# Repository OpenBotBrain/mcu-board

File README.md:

# mcu-board

Some design notes for an MCU board...
Deeply WIP.

## Features

1. STM32 Cortex M4 with FSMC (possibility: STM32F413ZGT6 for 144-LQFP,
   STM32F413VGT3 for 100-LQFP, and STM32F413RGT6 for 64-LQFP)
2. Extra flash and PSRAM
2. WIFI module e.g. [ESP32 C3](https://www.espressif.com/sites/default/files/documentation/esp32-c3-mini-1_datasheet_en.pdf) or [ESP32 S3](https://www.espressif.com/sites/default/files/documentation/esp32-s3-mini-1_mini-1u_datasheet_en.pdf)
3. 4 motor control ports (EV3 compatible)
4. 4 sensor control ports (EV3 compatible)
5. Raspberry Pi pin-out connector (enough to communicate with
   Raspberry pi Zero, does not need full support)
5. SD card (SPI interface enough/SDIO nice to have but requires supported MCU)
6. Accelerometer (could be external)
7. STEMMA QT connector (nice to have)
8. Some informative display (nice to have)
9. A couple of buttons for interface (nice to have also)
10. Lego "compatible" physical shape.

### Alternative

- STM32L4R5VGT6 with 640KB of RAM instead of the external ram versions
  (but it also supports the FMC/FSMC). And it is cheap, and more
  available than the previous ones. (Or the subtly better STM32L4R5VIT6)

### Notes

- The [WIFI
  module](https://www.digikey.co.uk/en/products/detail/espressif-systems/ESP32-C3-MINI-1-H4/14548892)
  with the SD card on one side and the Raspberry Pi connector may not
  need to be active at the same time.
- The display could be controlled by the WIFI module via [AT
  commands](https://docs.espressif.com/projects/esp-at/en/latest/esp32/Compile_and_Develop/How_to_add_user-defined_AT_commands.html).
  Other things could be moved to the WIFI module too (the interface
  buttons, maybe).
- The board would be a [Raspberry Pi
  hat](https://github.com/raspberrypi/hats) that can work alone. This
  can be a rev 2 objective, but planning for the space would not hurt.
- Driving external memories with the FSMC, application not AN4761

# smaller mcu-board

## Features

1. STM32 Cortex M4 - May be
   - STM32L4P5CGT6
   - STM32L4P5CGT6P
   - STM32L4Q5CGT6
   - STM32L4Q5CGT6P
all (48-LQFP with 1MB of flash, and 320KB of RAM).

2. WIFI module e.g. [ESP32 C3](https://www.espressif.com/sites/default/files/documentation/esp32-c3-mini-1_datasheet_en.pdf) or [ESP32 S3](https://www.espressif.com/sites/default/files/documentation/esp32-s3-mini-1_mini-1u_datasheet_en.pdf)

3. 4 motor control ports (EV3 compatible)
4. 4 sensor control ports (EV3 compatible)

5. Raspberry Pi pin-out connector (enough to communicate with
   Raspberry pi Zero, does not need full support)

5. SD card (SPI interface enough/SDIO nice to have but requires supported MCU)
6. Accelerometer (could be external)
7. STEMMA QT connector (nice to have)
8. Some informative display and a couple of LEDs (nice to have)
9. A couple of buttons for interface (nice to have also)
10. Lego "compatible" physical shape.

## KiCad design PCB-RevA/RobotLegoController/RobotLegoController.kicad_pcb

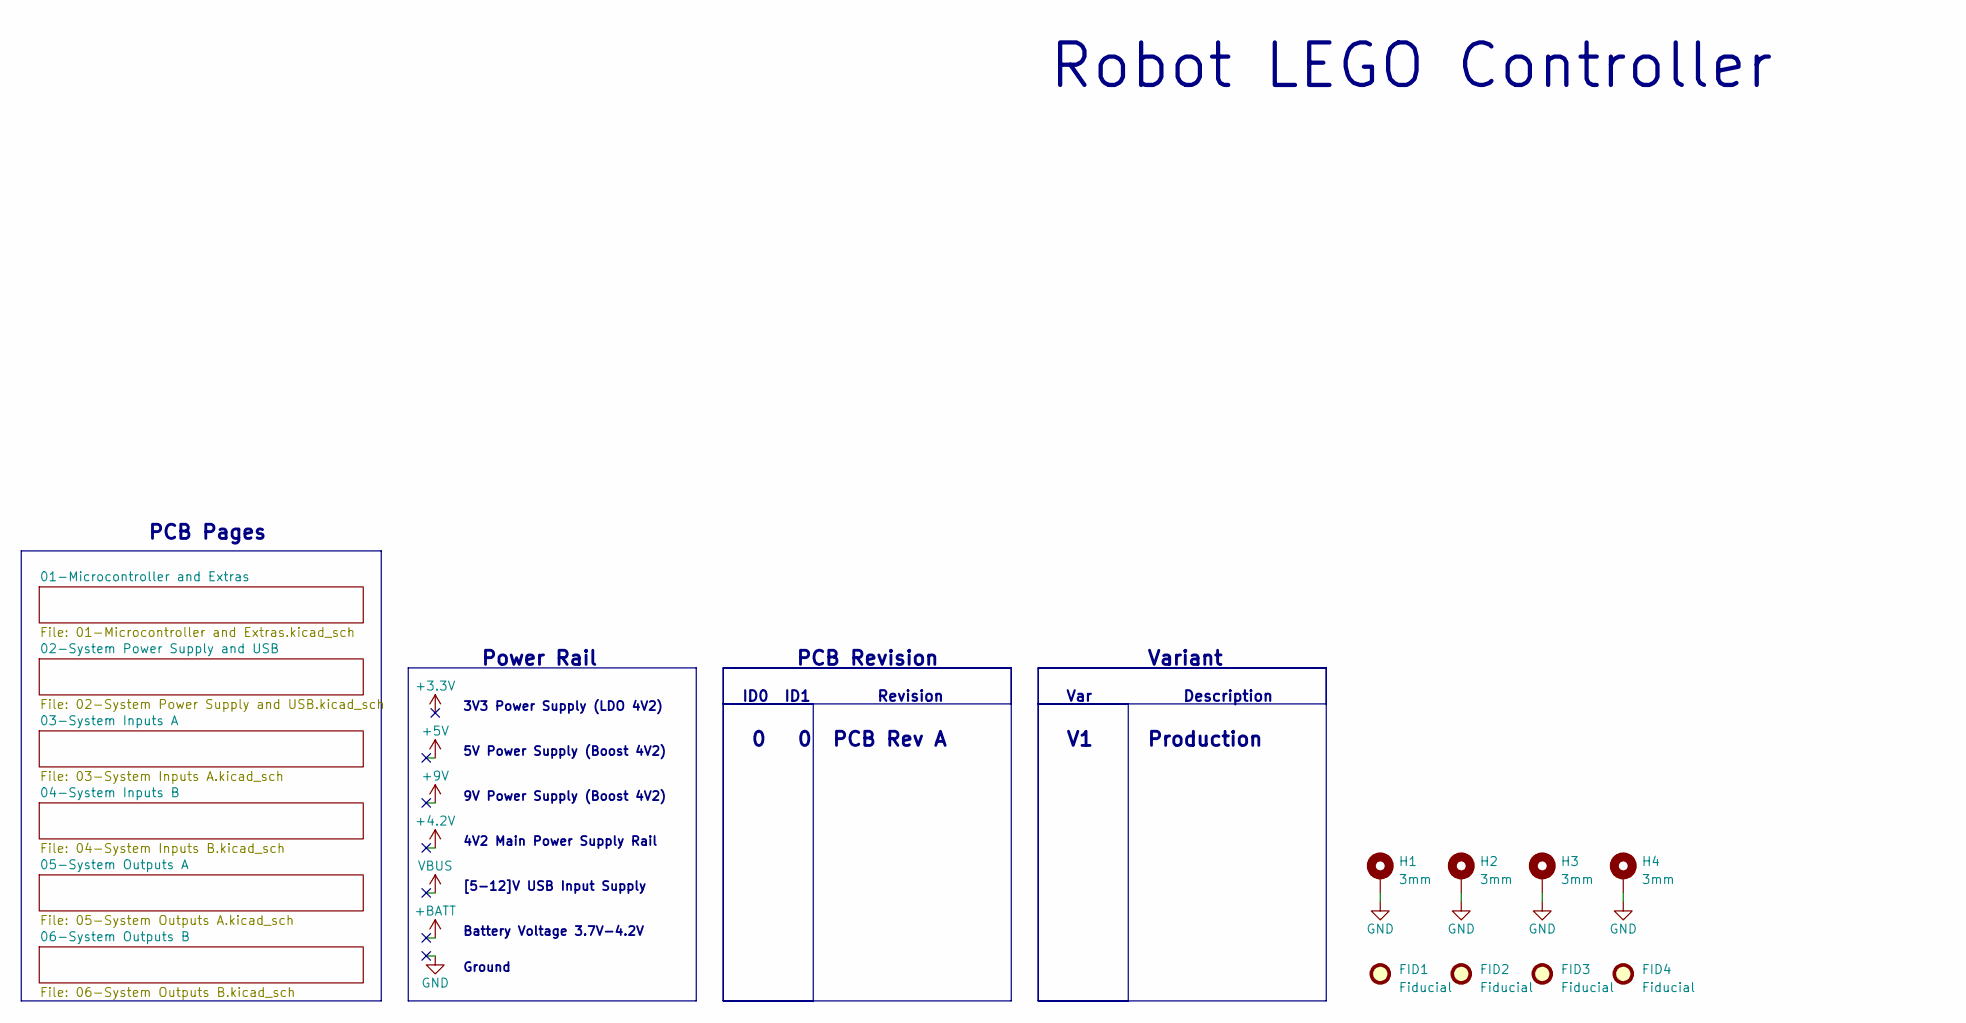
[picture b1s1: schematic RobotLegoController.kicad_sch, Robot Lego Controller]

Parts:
FID1, FID2, FID3, FID4: Fiducial; Fiducial_1mm_Mask3mm
H1, H2, H3, H4: 3mm; MountingHole_3.2mm_M3_Pad

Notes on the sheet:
Power Rail
Var
0 0
ID0 ID1
9V Power Supply (Boost 4V2)
3V3 Power Supply (LDO 4V2)
Battery Voltage 3.7V-4.2V
Variant
[5-12]V USB Input Supply
Description
Production
PCB Revision
PCB Rev A
4V2 Main Power Supply Rail
Revision
PCB Pages
Ground
5V Power Supply (Boost 4V2)
Robot LEGO Controller

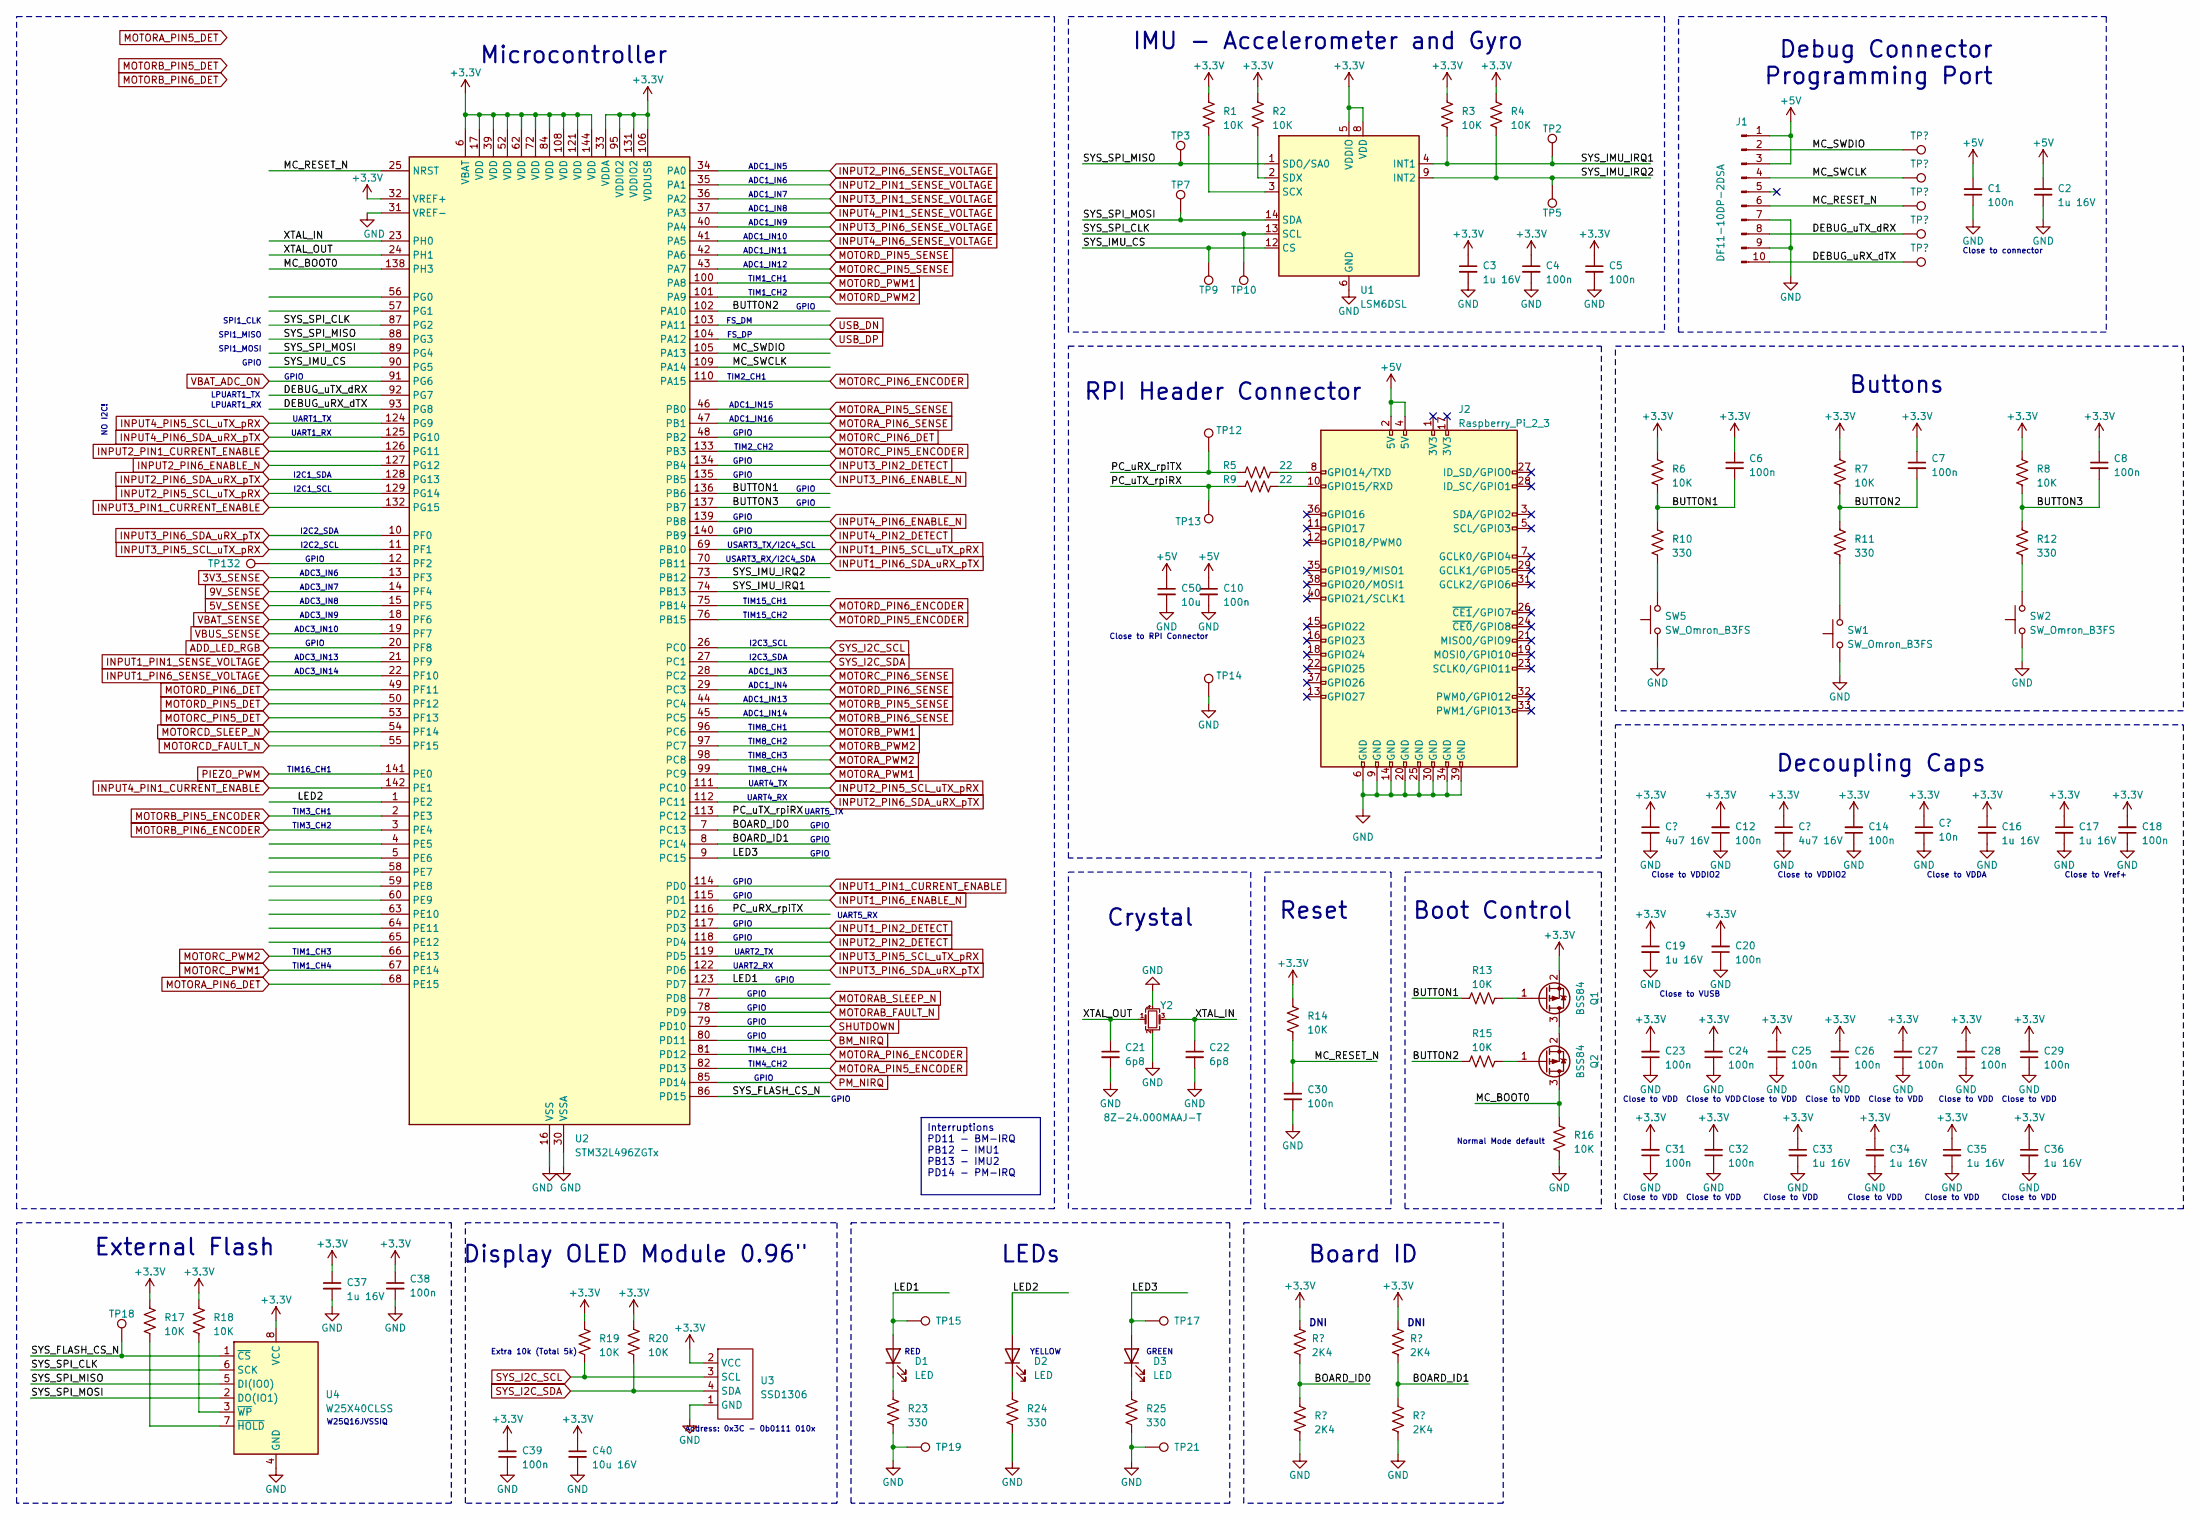
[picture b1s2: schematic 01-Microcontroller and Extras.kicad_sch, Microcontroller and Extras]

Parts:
C1, C4, C5, C6, C7, C8, C10, C12, C14, C18, C20, C23, C24, C25, C26, C27, C28, C29, C30, C31, C32, C38, C39: 100n; C_0402_1005Metric
C2, C3, C16, C17, C19, C33, C34, C35, C36, C37: 1u 16V; C_0603_1608Metric
C11, C13: 4u7 16V; C_0603_1608Metric
C15: 10n; C_0402_1005Metric
C21, C22: 6p8; C_0402_1005Metric
C40: 10u 16V; C_0805_2012Metric
C50: 10u; C_0805_2012Metric
D1, D2, D3: LED; LED_0402_1005Metric
J1: DF11-10DP-2DSA; JST_PHD_B10B-PHDSS_2x05_P2.00mm_Vertical
J2: Raspberry_Pi_2_3; PinHeader_2x20_P2.54mm_Vertical
Q1, Q2: BSS84; SOT-23
R1, R2, R3, R4, R6, R7, R8, R13, R14, R15, R16, R17, R18, R19, R20: 10K; R_0402_1005Metric
R5, R9: 22; R_0402_1005Metric
R10, R11, R12, R23, R24, R25: 330; R_0402_1005Metric
R21, R22, R26, R27: 2K4; R_0402_1005Metric
SW1, SW2, SW5: SW_Omron_B3FS; SW_Push_1P1T_NO_6x6mm_H9.5mm
TP1, TP2, TP3, TP4, TP5, TP6, TP7, TP8, TP9, TP10, TP11, TP12, TP13, TP14, TP18, TP132: S1mm; TestPoint_Pad_1.0x1.0mm
TP15, TP17, TP19, TP21: TH1mm; TestPoint_THTPad_1.0x1.0mm_Drill0.5mm
U1: LSM6DSL; LGA-14_3x2.5mm_P0.5mm_LayoutBorder3x4y
U2: STM32L496ZGTx; LQFP-144_20x20mm_P0.5mm
U3: SSD1306; 128x64OLED
U4: W25X40CLSS; SOIC-8_5.275x5.275mm_P1.27mm
Y2: 8Z-24.000MAAJ-T; Crystal_SMD_Abracon_ABM10-4Pin_2.5x2.0mm

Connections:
3V3_SENSE: U2.13 (PF3); also elsewhere on the board
5V_SENSE: U2.15 (PF5); also elsewhere on the board
9V_SENSE: U2.14 (PF4); also elsewhere on the board
+3.3V: C3.1, C4.1, C5.1, C6.1, C7.1, C8.1, C11.1, C12.2, C13.1, C14.2, C15.1, C16.1, C17.1, C18.2, C19.1, C20.2, C23.2, C24.2, C25.2, C26.2, C27.2, C28.2, C29.2, C31.2, C32.2, C33.1, C34.1, C35.1, C36.1, C37.1, C38.1, C39.2, C40.1, Q1.2 (S), R1.2, R2.2, R3.2, R4.2, R6.2, R7.2, R8.2, R14.2, R17.2, R18.2, R19.2, R20.2, R21.2, R22.2, U1.5 (VDDIO), U1.8 (VDD), U2.6 (VBAT), U2.17 (VDD), U2.32 (VREF+), U2.33 (VDDA), U2.39 (VDD), U2.52 (VDD), U2.62 (VDD), U2.72 (VDD), U2.84 (VDD), U2.95 (VDDIO2), U2.106 (VDDUSB), U2.108 (VDD), U2.121 (VDD), U2.131 (VDDIO2), U2.144 (VDD), U3.2 (VCC), U4.8 (VCC); also elsewhere on the board
/01-Microcontroller and Extras/BOARD_ID0: R21.1, R26.2, U2.7 (PC13)
/01-Microcontroller and Extras/BOARD_ID1: R22.1, R27.2, U2.8 (PC14)
/01-Microcontroller and Extras/BUTTON1: C6.2, R6.1, R10.2, R13.2, U2.136 (PB6)
/01-Microcontroller and Extras/BUTTON2: C7.2, R7.1, R11.2, R15.2, U2.102 (PA10)
/01-Microcontroller and Extras/BUTTON3: C8.2, R8.1, R12.2, U2.137 (PB7)
/01-Microcontroller and Extras/DEBUG_uRX_dTX: J1.10, TP11.1, U2.93 (PG8)
/01-Microcontroller and Extras/DEBUG_uTX_dRX: J1.8, TP8.1, U2.92 (PG7)
/01-Microcontroller and Extras/LED1: D1.2 (A), TP15.1, U2.123 (PD7)
/01-Microcontroller and Extras/LED2: D2.2 (A), U2.1 (PE2)
/01-Microcontroller and Extras/LED3: D3.2 (A), TP17.1, U2.9 (PC15)
/01-Microcontroller and Extras/MC_BOOT0: Q2.3 (D), R16.1, U2.138 (PH3)
/01-Microcontroller and Extras/MC_RESET_N: C30.1, J1.6, R14.1, TP6.1, U2.25 (NRST)
/01-Microcontroller and Extras/MC_SWCLK: J1.4, TP4.1, U2.109 (PA14)
/01-Microcontroller and Extras/MC_SWDIO: J1.2, TP1.1, U2.105 (PA13)
/01-Microcontroller and Extras/PC_uRX_rpiTX: R5.1, TP12.1, U2.116 (PD2)
/01-Microcontroller and Extras/PC_uTX_rpiRX: R9.1, TP13.1, U2.113 (PC12)
/01-Microcontroller and Extras/SYS_FLASH_CS_N: TP18.1, U2.86 (PD15), U4.1 (~CS)
/01-Microcontroller and Extras/SYS_IMU_CS: TP9.1, U1.12 (CS), U2.90 (PG5)
/01-Microcontroller and Extras/SYS_IMU_IRQ1: R3.1, TP2.1, U1.4 (INT1), U2.74 (PB13)
/01-Microcontroller and Extras/SYS_IMU_IRQ2: R4.1, TP5.1, U1.9 (INT2), U2.73 (PB12)
/01-Microcontroller and Extras/SYS_SPI_CLK: TP10.1, U1.13 (SCL), U2.87 (PG2), U4.6 (SCK)
/01-Microcontroller and Extras/SYS_SPI_MISO: TP3.1, U1.1 (SDO/SA0), U2.88 (PG3), U4.5 (DI(IO0))
/01-Microcontroller and Extras/SYS_SPI_MOSI: TP7.1, U1.14 (SDA), U2.89 (PG4), U4.2 (DO(IO1))
/01-Microcontroller and Extras/XTAL_IN: C22.1, U2.23 (PH0), Y2.3
/01-Microcontroller and Extras/XTAL_OUT: C21.1, U2.24 (PH1), Y2.1
ADD_LED_RGB: U2.20 (PF8); also elsewhere on the board
BM_NIRQ: U2.80 (PD11); also elsewhere on the board
INPUT1_PIN1_CURRENT_ENABLE: U2.114 (PD0); also elsewhere on the board
INPUT1_PIN1_SENSE_VOLTAGE: U2.21 (PF9); also elsewhere on the board
INPUT1_PIN2_DETECT: U2.117 (PD3); also elsewhere on the board
INPUT1_PIN5_SCL_uTX_pRX: U2.69 (PB10); also elsewhere on the board
INPUT1_PIN6_ENABLE_N: U2.115 (PD1); also elsewhere on the board
INPUT1_PIN6_SDA_uRX_pTX: U2.70 (PB11); also elsewhere on the board
INPUT1_PIN6_SENSE_VOLTAGE: U2.22 (PF10); also elsewhere on the board
INPUT2_PIN1_CURRENT_ENABLE: U2.126 (PG11); also elsewhere on the board
INPUT2_PIN1_SENSE_VOLTAGE: U2.35 (PA1); also elsewhere on the board
INPUT2_PIN2_DETECT: U2.118 (PD4); also elsewhere on the board
INPUT2_PIN5_SCL_uTX_pRX: U2.111 (PC10), U2.129 (PG14); also elsewhere on the board
INPUT2_PIN6_ENABLE_N: U2.127 (PG12); also elsewhere on the board
INPUT2_PIN6_SDA_uRX_pTX: U2.112 (PC11), U2.128 (PG13); also elsewhere on the board
INPUT2_PIN6_SENSE_VOLTAGE: U2.34 (PA0); also elsewhere on the board
INPUT3_PIN1_CURRENT_ENABLE: U2.132 (PG15); also elsewhere on the board
INPUT3_PIN1_SENSE_VOLTAGE: U2.36 (PA2); also elsewhere on the board
INPUT3_PIN2_DETECT: U2.134 (PB4); also elsewhere on the board
INPUT3_PIN5_SCL_uTX_pRX: U2.11 (PF1), U2.119 (PD5); also elsewhere on the board
INPUT3_PIN6_ENABLE_N: U2.135 (PB5); also elsewhere on the board
INPUT3_PIN6_SDA_uRX_pTX: U2.10 (PF0), U2.122 (PD6); also elsewhere on the board
INPUT3_PIN6_SENSE_VOLTAGE: U2.40 (PA4); also elsewhere on the board
INPUT4_PIN1_CURRENT_ENABLE: U2.142 (PE1); also elsewhere on the board
INPUT4_PIN2_DETECT: U2.140 (PB9); also elsewhere on the board
INPUT4_PIN5_SCL_uTX_pRX: U2.124 (PG9); also elsewhere on the board
INPUT4_PIN6_ENABLE_N: U2.139 (PB8); also elsewhere on the board
INPUT4_PIN6_SDA_uRX_pTX: U2.125 (PG10); also elsewhere on the board
INPUT4_PIN6_SENSE_VOLTAGE: U2.41 (PA5); also elsewhere on the board
MOTORAB_FAULT_N: U2.78 (PD9); also elsewhere on the board
MOTORAB_SLEEP_N: U2.77 (PD8); also elsewhere on the board
MOTORA_PIN5_ENCODER: U2.82 (PD13); also elsewhere on the board
MOTORA_PIN6_DET: U2.68 (PE15); also elsewhere on the board
MOTORA_PIN6_ENCODER: U2.81 (PD12); also elsewhere on the board
MOTORA_PWM1: U2.99 (PC9); also elsewhere on the board
MOTORA_PWM2: U2.98 (PC8); also elsewhere on the board
MOTORB_PIN6_ENCODER: U2.3 (PE4); also elsewhere on the board
MOTORB_PWM1: U2.96 (PC6); also elsewhere on the board
MOTORB_PWM2: U2.97 (PC7); also elsewhere on the board
MOTORCD_FAULT_N: U2.55 (PF15)
MOTORCD_SLEEP_N: U2.54 (PF14); also elsewhere on the board
MOTORC_PIN5_DET: U2.53 (PF13); also elsewhere on the board
MOTORC_PIN6_DET: U2.48 (PB2); also elsewhere on the board
MOTORC_PWM1: U2.67 (PE14); also elsewhere on the board
MOTORC_PWM2: U2.66 (PE13); also elsewhere on the board
MOTORD_PIN5_DET: U2.50 (PF12); also elsewhere on the board
MOTORD_PIN6_DET: U2.49 (PF11); also elsewhere on the board
MOTORD_PWM1: U2.100 (PA8); also elsewhere on the board
MOTORD_PWM2: U2.101 (PA9); also elsewhere on the board
unnamed: D1.1 (K), R23.2
unnamed: D2.1 (K), R24.2
unnamed: D3.1 (K), R25.2
unnamed: J2.8 (GPIO14/TXD), R5.2
unnamed: J2.10 (GPIO15/RXD), R9.2
unnamed: Q1.3 (D), Q2.2 (S)
unnamed: Q1.1 (G), R13.1
unnamed: Q2.1 (G), R15.1
unnamed: R11.1, SW1.2
unnamed: R12.1, SW2.2
unnamed: R1.1, U1.3 (SCX)
unnamed: R2.1, U1.2 (SDX)
unnamed: TP132.1, U2.12 (PF2)
unnamed: R17.1, U4.7 (~HOLD)
unnamed: R18.1, U4.3 (~WP)
PIEZO_PWM: U2.141 (PE0); also elsewhere on the board
PM_NIRQ: U2.85 (PD14); also elsewhere on the board
SHUTDOWN: U2.79 (PD10); also elsewhere on the board
SYS_I2C_SCL: R19.1, U2.26 (PC0), U3.3 (SCL); also elsewhere on the board
SYS_I2C_SDA: R20.1, U2.27 (PC1), U3.4 (SDA); also elsewhere on the board
USB_DN: U2.103 (PA11); also elsewhere on the board
USB_DP: U2.104 (PA12); also elsewhere on the board
VBAT_ADC_ON: U2.91 (PG6); also elsewhere on the board
VBAT_SENSE: U2.18 (PF6); also elsewhere on the board
VBUS_SENSE: U2.19 (PF7); also elsewhere on the board

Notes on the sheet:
Interruptions PD11 - BM-IRQ PB12 - IMU1 PB13 - IMU2 PD14 - PM-IRQ
TIM15_CH1
I2C3_SDA
TIM2_CH1
Close to connector
Buttons
Display OLED Module 0.96"
GPIO
ADC1_IN16
ADC1_IN13
UART1_RX
UART2_RX
ADC1_IN3
ADC3_IN7
TIM1_CH4
Address: 0x3C - 0b0111 010x
TIM8_CH1
TIM8_CH3
Close to VDD
Close to RPI Connector
USART3_TX/I2C4_SCL
External Flash
UART5_TX
TIM1_CH3
Close to VUSB
UART2_TX
DNI
I2C2_SCL
ADC1_IN5
UART5_RX
LPUART1_TX
ADC1_IN10
W25Q16JVSSIQ
Boot Control
FS_DP
USART3_RX/I2C4_SDA
TIM8_CH2
SPI1_CLK
UART4_RX
I2C3_SCL

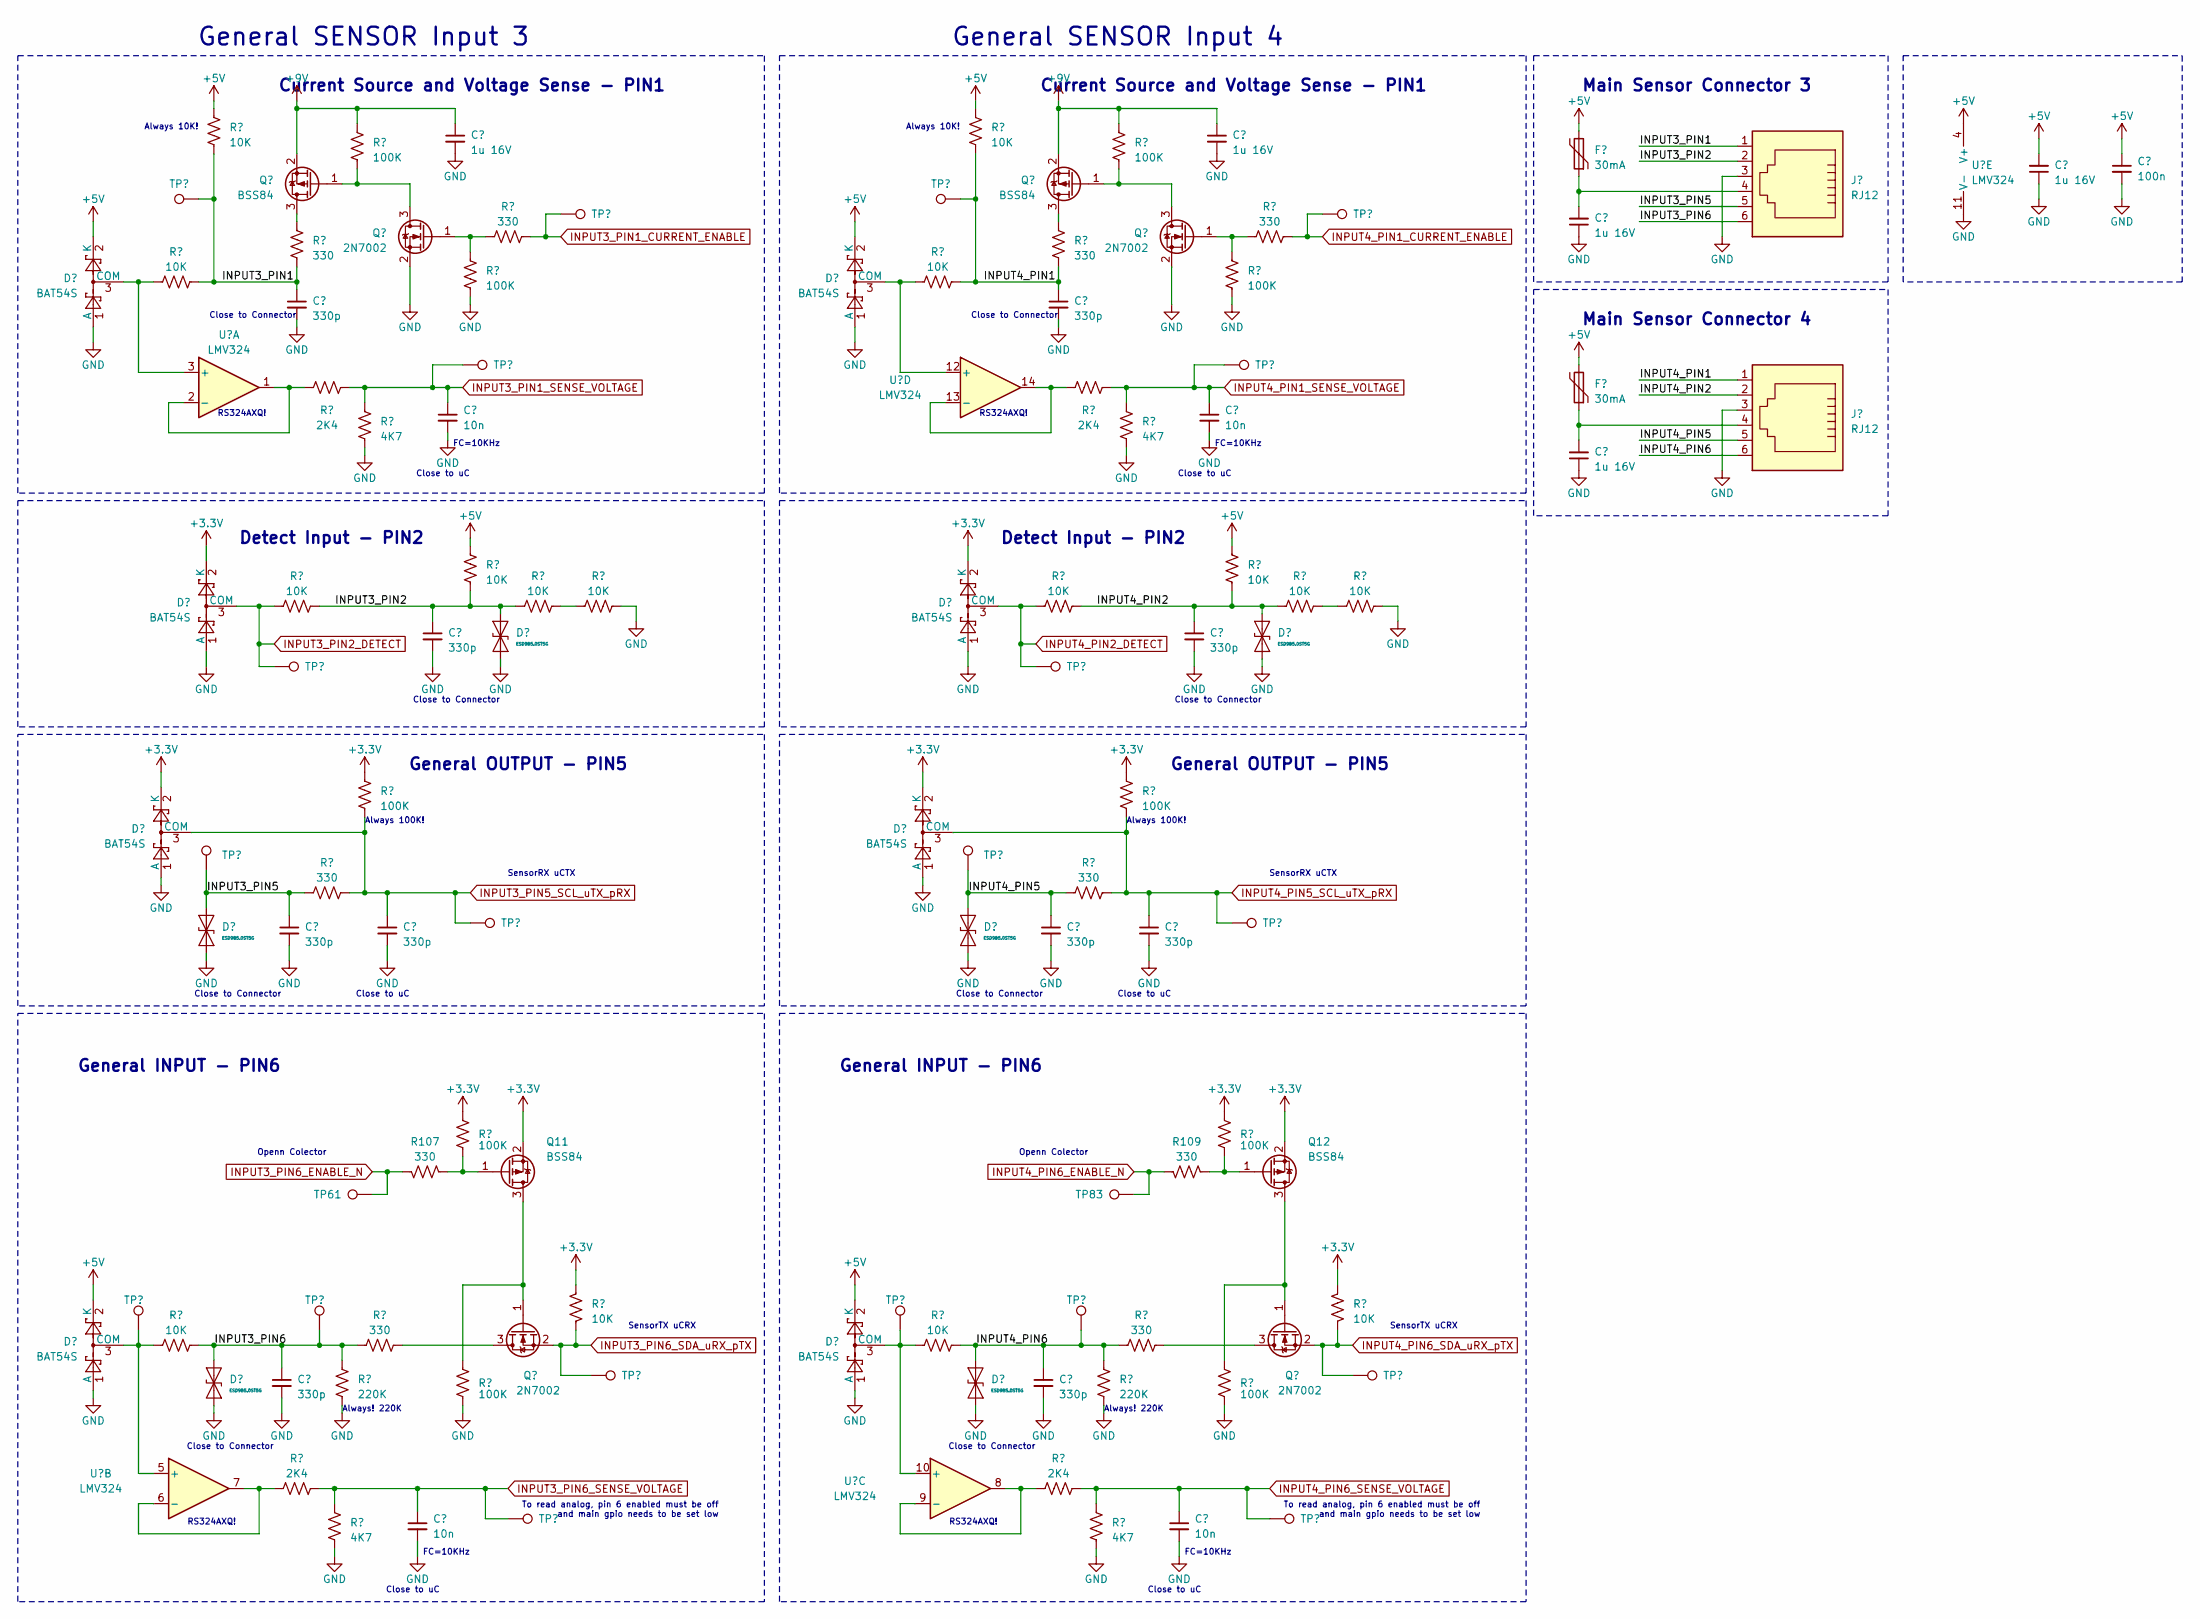
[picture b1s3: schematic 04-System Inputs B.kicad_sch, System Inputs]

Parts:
C110, C111, C112, C114, C119: 1u 16V; C_0603_1608Metric
C113: 100n; C_0402_1005Metric
C115, C116, C120, C121, C122, C123, C124, C125, C126, C127: 330p; C_0402_1005Metric
C117, C118, C128, C129: 10n; C_0402_1005Metric
D27, D28, D29, D30, D33, D34, D37, D38: BAT54S; SOT-23
D31, D32, D35, D36, D39, D40: ESD9B5.0ST5G; D_SOD-923
F5, F6: 30mA; R_0603_1608Metric
J9, J10: RJ12; RJ12_Amphenol_54601
Q11, Q12, Q17, Q18: BSS84; SOT-23
Q19, Q20, Q27, Q28: 2N7002; SOT-23
R106, R108, R126, R127, R132, R133, R148, R149, R167, R169: 100K; R_0402_1005Metric
R107, R109, R128, R129, R130, R131, R150, R151, R163, R165: 330; R_0402_1005Metric
R124, R125, R134, R135, R140, R141, R142, R143, R144, R145, R146, R147, R160, R161, R162, R164: 10K; R_0402_1005Metric
R136, R137, R170, R171: 2K4; R_0402_1005Metric
R138, R139, R172, R173: 4K7; R_0402_1005Metric
R166, R168: 220K; R_0402_1005Metric
TP61, TP70, TP71, TP72, TP73, TP74, TP75, TP76, TP77, TP78, TP79, TP80, TP81, TP83, TP86, TP87, TP88, TP89, TP90, TP91, TP92, TP93: S1mm; TestPoint_Pad_1.0x1.0mm
U11: LMV324; SOIC-14_3.9x8.7mm_P1.27mm

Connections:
+3.3V: D29.2 (K), D30.2 (K), D33.2 (K), D34.2 (K), Q11.2 (S), Q12.2 (S), R106.2, R108.2, R148.2, R149.2, R160.1, R161.1; also elsewhere on the board
+9V: C110.1, C111.1, Q17.2 (S), Q18.2 (S), R126.2, R127.2; also elsewhere on the board
/04-System Inputs B/INPUT3_PIN1: C115.1, J9.1, R124.1, R130.1, R134.1, TP70.1
/04-System Inputs B/INPUT3_PIN2: C120.1, D31.2 (A2), J9.2, R140.1, R142.2, R143.2
/04-System Inputs B/INPUT3_PIN5: C122.1, D35.2 (A2), J9.5, R150.2, TP78.1
/04-System Inputs B/INPUT3_PIN6: C126.1, D39.2 (A2), J9.6, R162.2, R163.2, R166.1, TP87.1
/04-System Inputs B/INPUT4_PIN1: C116.1, J10.1, R125.1, R131.1, R135.1, TP71.1
/04-System Inputs B/INPUT4_PIN2: C121.1, D32.2 (A2), J10.2, R141.1, R145.2, R146.2
/04-System Inputs B/INPUT4_PIN5: C124.1, D36.2 (A2), J10.5, R151.2, TP79.1
INPUT3_PIN1_CURRENT_ENABLE: R128.1, TP72.1; also elsewhere on the board
INPUT3_PIN1_SENSE_VOLTAGE: C117.1, R136.2, R138.1, TP74.1; also elsewhere on the board
INPUT3_PIN2_DETECT: D29.3 (COM), R142.1, TP76.1; also elsewhere on the board
INPUT3_PIN5_SCL_uTX_pRX: C123.1, D33.3 (COM), R148.1, R150.1, TP80.1; also elsewhere on the board
INPUT3_PIN6_ENABLE_N: R107.1, TP61.1; also elsewhere on the board
INPUT3_PIN6_SDA_uRX_pTX: Q27.2 (S), R160.2, TP90.1; also elsewhere on the board
INPUT3_PIN6_SENSE_VOLTAGE: C128.1, R170.2, R172.1, TP92.1; also elsewhere on the board
INPUT4_PIN1_CURRENT_ENABLE: R129.1, TP73.1; also elsewhere on the board
INPUT4_PIN2_DETECT: D30.3 (COM), R145.1, TP77.1; also elsewhere on the board
INPUT4_PIN5_SCL_uTX_pRX: C125.1, D34.3 (COM), R149.1, R151.1, TP81.1; also elsewhere on the board
INPUT4_PIN6_ENABLE_N: R109.1, TP83.1; also elsewhere on the board
INPUT4_PIN6_SDA_uRX_pTX: Q28.2 (S), R161.2, TP91.1; also elsewhere on the board
INPUT4_PIN6_SENSE_VOLTAGE: C129.1, R171.2, R173.1, TP93.1; also elsewhere on the board
unnamed: C114.2, F5.1, J9.4
unnamed: C119.2, F6.1, J10.4
unnamed: D27.3 (COM), R134.2, U11.3 (+)
unnamed: D28.3 (COM), R135.2, U11.12 (+)
unnamed: D37.3 (COM), R162.1, TP86.1, U11.5 (+)
unnamed: D38.3 (COM), R164.1, TP88.1, U11.10 (+)
unnamed: Q11.3 (D), Q27.1 (G), R167.2
unnamed: Q11.1 (G), R106.1, R107.2
unnamed: Q12.3 (D), Q28.1 (G), R169.2
unnamed: Q12.1 (G), R108.1, R109.2
unnamed: Q17.3 (D), R130.2
unnamed: Q17.1 (G), Q19.3 (D), R126.1
unnamed: Q18.3 (D), R131.2
unnamed: Q18.1 (G), Q20.3 (D), R127.1
unnamed: Q19.1 (G), R128.2, R132.2
unnamed: Q20.1 (G), R129.2, R133.2
unnamed: Q27.3 (D), R163.1
unnamed: Q28.3 (D), R165.1
unnamed: R143.1, R144.2
unnamed: R146.1, R147.2
unnamed: R136.1, U11.1, U11.2 (-)
unnamed: R170.1, U11.6 (-), U11.7
unnamed: R171.1, U11.8, U11.9 (-)
unnamed: R137.1, U11.13 (-), U11.14

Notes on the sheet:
Always 10K!
Openn Colector
General SENSOR Input 3
General OUTPUT - PIN5
FC=10KHz
Close to uC
SensorTX uCRX
Close to Connector
RS324AXQ!
SensorRX uCTX
Current Source and Voltage Sense - PIN1
To read analog, pin 6 enabled must be off and main gpio needs to be set low
Always 100K!
General SENSOR Input 4
Detect Input - PIN2
Always! 220K
Main Sensor Connector 4
General INPUT - PIN6
Main Sensor Connector 3
